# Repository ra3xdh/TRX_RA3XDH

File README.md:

## Описание

Схема и печатная плата для улучшенной версии моего трансивера из журнала Радио №2, 2009.

Видео его работы здесь: https://www.youtube.com/watch?v=EY1k9Iahgxw

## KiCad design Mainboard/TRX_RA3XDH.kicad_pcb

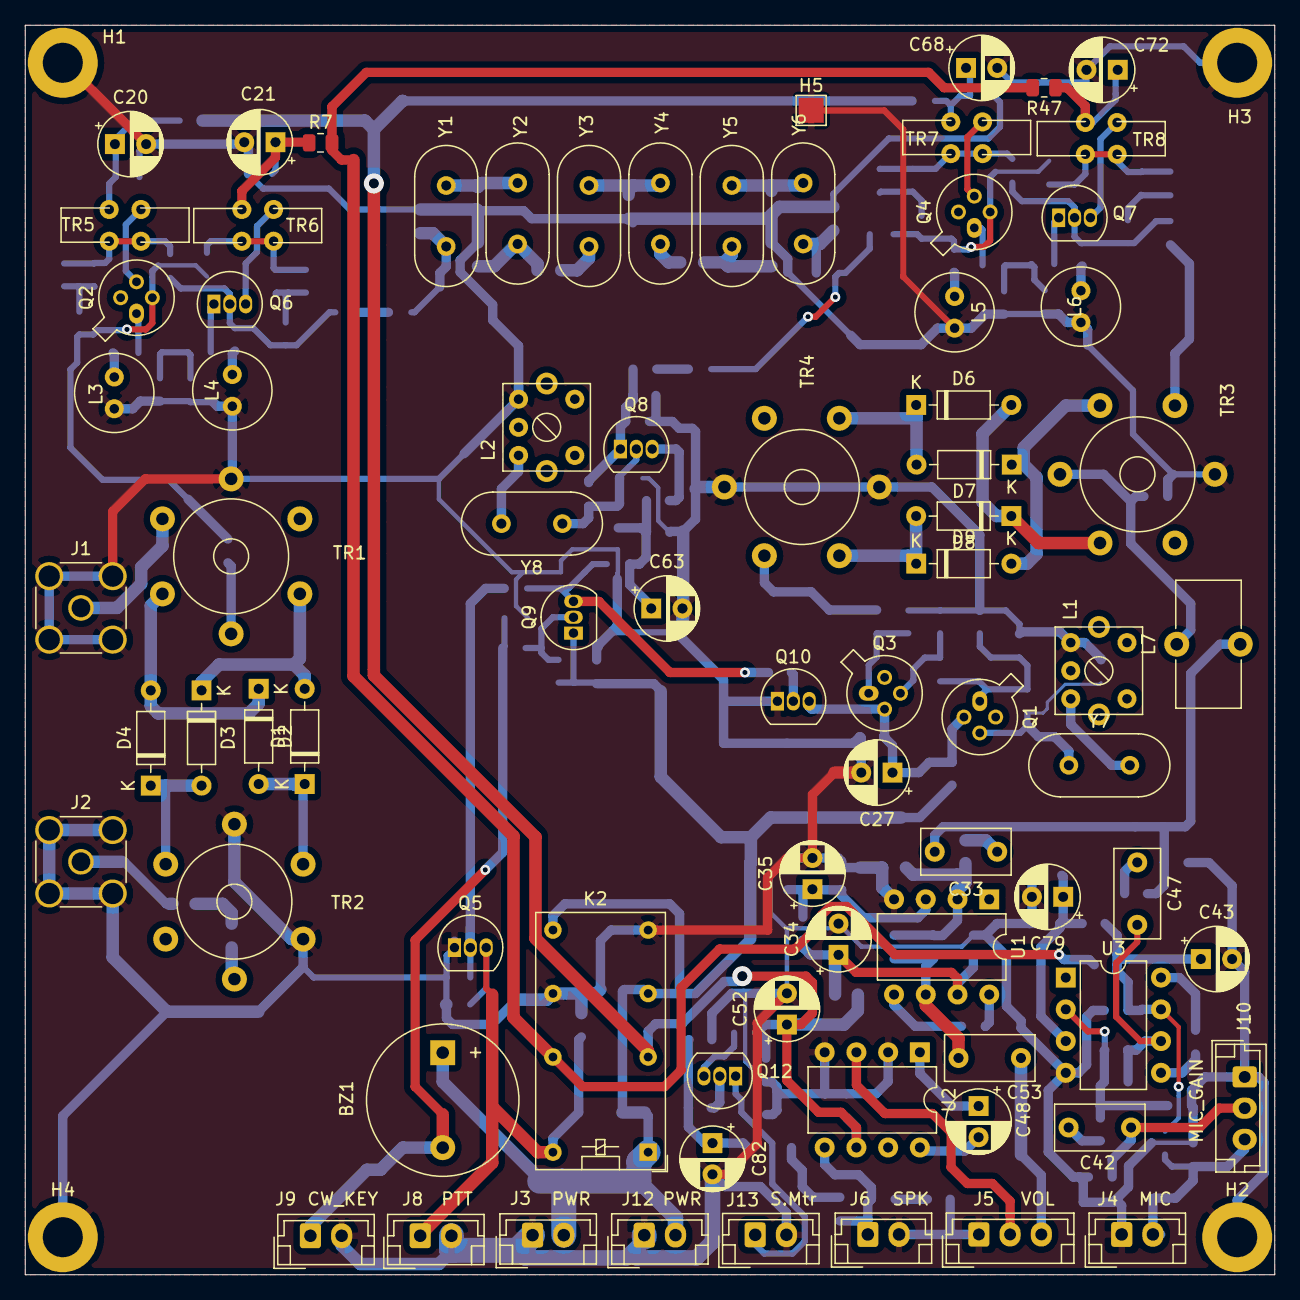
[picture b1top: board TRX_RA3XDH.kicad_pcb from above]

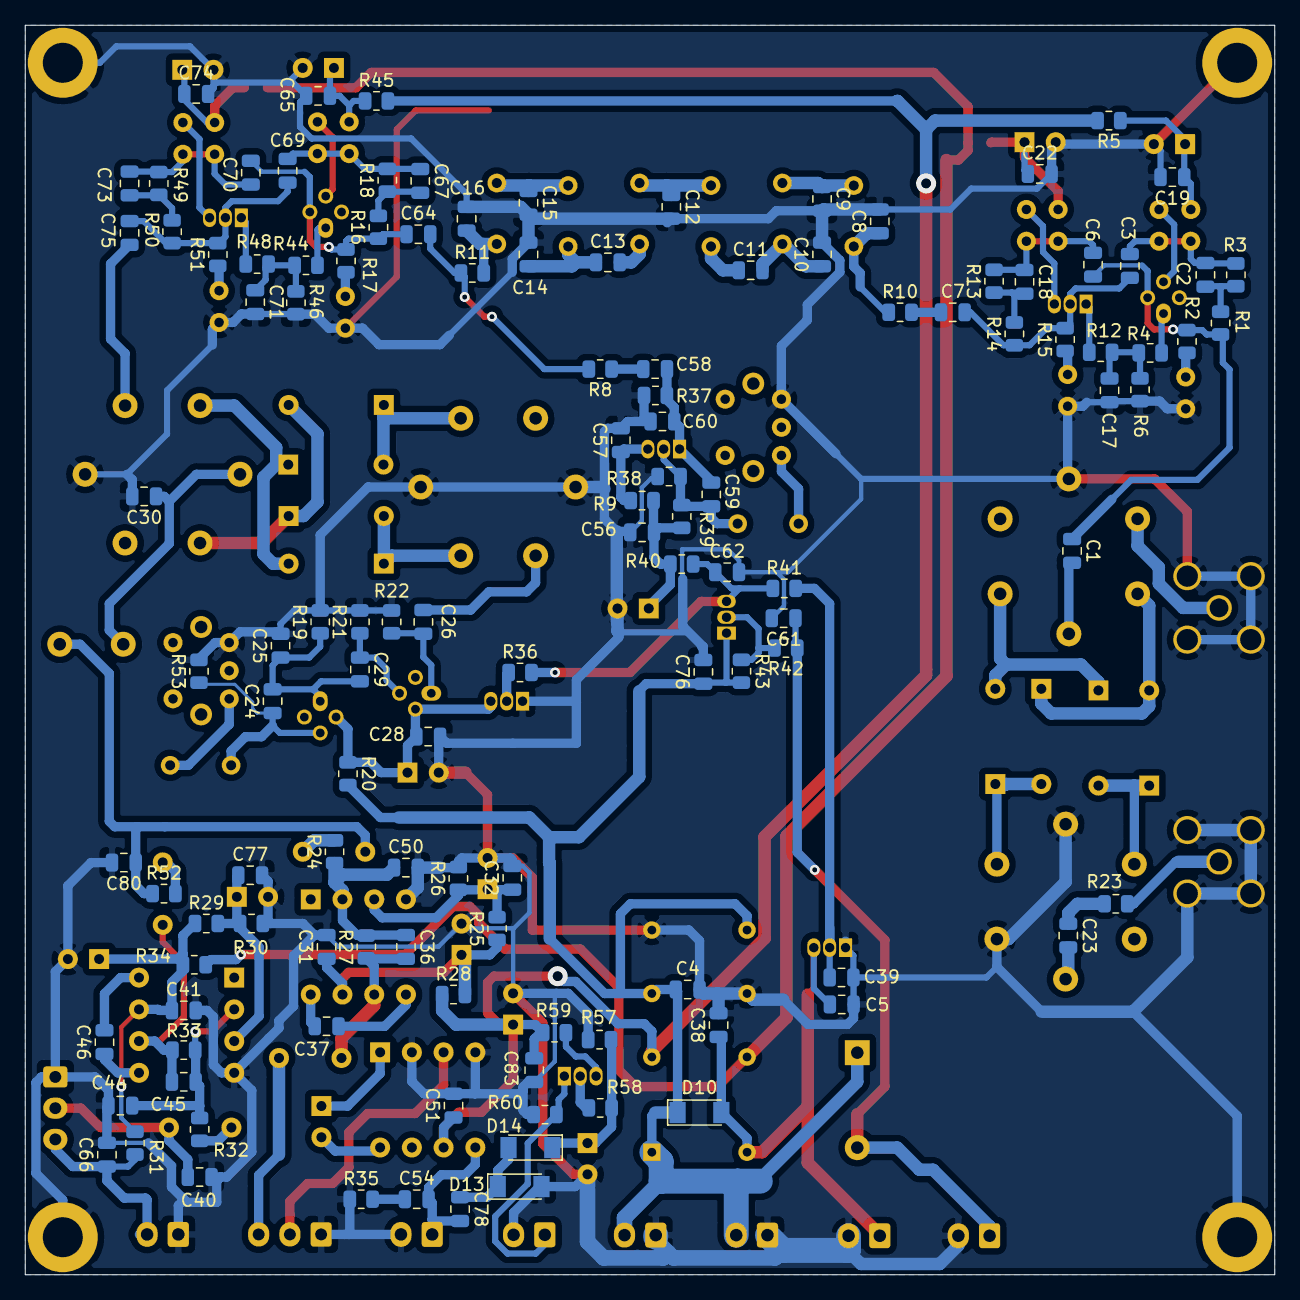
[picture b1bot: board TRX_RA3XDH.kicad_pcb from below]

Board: 2 copper layers, 100.0 x 100.0 mm, 203 parts (121 on the bottom side), 108 nets.

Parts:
BZ1: Buzzer; Buzzer_12x9.5RM7.6
C1, C3, C6, C7, C23, C26, C64, C69, C70: 10n; C_0805_2012Metric
C2, C4, C5, C17, C18, C19, C22, C28, C31, C32, C38, C39, C41, C51, C54, C56, C57, C61, C62, C65, C67, C71, C73, C74, C75, C76, C77, C78, C83: 0.1u; C_0805_2012Metric
C8, C16: 43p; C_0805_2012Metric
C9, C15: 94p; C_0805_2012Metric
C10, C14: 120p; C_0805_2012Metric
C11, C13: 370p; C_0805_2012Metric
C12: 130p; C_0805_2012Metric
C20, C21, C27, C34, C35, C43, C48, C52, C63, C68, C72, C79: 10u; CP_Radial_D5.0mm_P2.50mm
C24, C25, C58, C59, C60: 22p; C_0805_2012Metric
C29, C37, C46: 33p; C_0805_2012Metric
C30, C40, C44, C50, C66, C80: 47n; C_0805_2012Metric
C33, C42, C47, C53: 1.0; C_Rect_L7.0mm_W3.5mm_P5.00mm
C36: 680p; C_0805_2012Metric
C45: 1000p; C_0805_2012Metric
C82: 4.7u; CP_Radial_D5.0mm_P2.50mm
D1, D2, D3, D4, D6, D7, D8, D9: 1N5711; D_DO-35_SOD27_P7.62mm_Horizontal
D10, D13, D14: LL4148; D_MiniMELF
H1, H2, H3, H4: GND; MountingHole_3.2mm_M3_DIN965_Pad
H5: gnd; TestPoint_Pad_2.0x2.0mm
J1: RF_INOUT; SMA_Amphenol_132291_Vertical
J2: VFO; SMA_Amphenol_132291_Vertical
J3, J12: PWR; JST_EH_B2B-EH-A_1x02_P2.50mm_Vertical
J4: MIC; JST_EH_B2B-EH-A_1x02_P2.50mm_Vertical
J5: VOL; JST_EH_B3B-EH-A_1x03_P2.50mm_Vertical
J6: SPK; JST_EH_B2B-EH-A_1x02_P2.50mm_Vertical
J8: PTT; JST_EH_B2B-EH-A_1x02_P2.50mm_Vertical
J9: CW_KEY; JST_EH_B2B-EH-A_1x02_P2.50mm_Vertical
J10: MIC_GAIN; JST_EH_B3B-EH-A_1x03_P2.50mm_Vertical
J13: S-Met.; JST_EH_B2B-EH-A_1x02_P2.50mm_Vertical
K2: G5V-2; Relay_DPDT_Omron_G5V-2
L1, L2: 3u; NEOSID_5t_4.5x4.5mm_132
L3, L4, L5, L6: 33u; L2.5x6
L7: 33u; L_Toroid_Vertical_L10.0mm_W5.0mm_P5.08mm
Q1, Q3: 2N4416; TO-72-4
Q2, Q4: 2N918; TO-72-4
Q5, Q6, Q7, Q8, Q10, Q12: 2N3904; TO-92_Inline
Q9: 2N3906; TO-92_Inline
R1, R2, R14, R15, R16, R17, R22, R50, R51: 470; R_0805_2012Metric
R3, R13, R18, R49: 2.2k; R_0805_2012Metric
R4, R12, R35, R44, R48: 4.7; R_0805_2012Metric
R5, R7, R8, R10, R11, R45, R47: 47; R_0805_2012Metric
R6, R9, R28, R34, R40, R46: 100; R_0805_2012Metric
R19, R20: 680; R_0805_2012Metric
R21, R53: 10k; R_0805_2012Metric
R23: 33; R_0805_2012Metric
R24, R32, R52, R60: 1k; R_0805_2012Metric
R25, R26, R29, R30, R31: 20k; R_0805_2012Metric
R27: 120k; R_0805_2012Metric
R33: 33k; R_0805_2012Metric
R36, R41, R42, R43: 22k; R_0805_2012Metric
R37: 360; R_0805_2012Metric
R38: 6.8k; R_0805_2012Metric
R39: 13k; R_0805_2012Metric
R57: 1M; R_0805_2012Metric
R58: 150k; R_0805_2012Metric
R59: 8.2k; R_0805_2012Metric
TR1, TR2, TR3, TR4: FT37-43; Transformer_Toroid_Tapped_Horizontal_D9.0mm_Amidon-T30
TR5, TR6, TR7, TR8: FT37-43; L_Toroid_Vertical_L10.0mm_W5.0mm_4pin
U1, U3: NE5534; DIP-8_W7.62mm
U2: LM386; DIP-8_W7.62mm
Y1, Y2, Y3, Y4, Y5, Y6, Y7, Y8: 8.867Mhz; Crystal_HC49-U_Vertical

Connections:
+12V: BZ1.1, C4.1, C76.1, D10.1, J3.2, J12.2, K2.1, K2.6, K2.9, Q9.1, R20.2, R43.2
/+12V_BFO2: C62.1, Q9.3, R36.2, R40.2, R41.1
/+12V_RX: C51.1, C52.1, C83.1, K2.4, R5.2, R28.1, R45.2, R59.2, U2.6
/+12V_TX: K2.13, R7.2, R34.1, R47.2
/CW_KEY: BZ1.2, C61.1, J9.1, R42.1
/MIC_IN: C40.1, C42.2, J10.2
/PTT: C5.1, C38.1, D10.2, J8.1, K2.16, Q5.3
/TX: C39.1, Q5.2, R41.2
/VGND_RX: C32.1, C35.1, R25.2, R26.1, U1.3
/VGND_TX: C77.1, C79.1, R29.2, R30.1, U3.3
/VOL_IN: C53.1, J5.3
/VOL_OUT: J5.2, U2.3
GND: C4.2, C5.2, C8.2, C9.2, C10.2, C12.2, C14.2, C15.2, C16.2, C17.2, C19.2, C20.2, C21.2, C22.2, C25.2, C27.2, C28.2, C30.2, C31.2, C32.2, C34.2, C35.2, C38.2, C39.2, C40.2, C41.2, C43.2, C44.2, C50.2, C51.2, C52.2, C56.2, C57.2, C60.2, C61.2, C62.2, C63.2, C65.2, C66.2, C68.2, C71.2, C72.2, C74.2, C76.2, C77.2, C79.2, C80.2, C82.2, C83.2, D13.2, H1.1, H2.1, H3.1, H4.1, H5.1, J1.2, J2.2, J3.1, J4.1, J5.1, J6.2, J8.2, J9.2, J10.1, J12.1, J13.2, K2.8, K2.11, L1.2, L2.2, L3.2, L4.2, L5.2, L6.2, Q5.1, Q10.1, R6.1, R19.2, R21.2, R22.2, R26.2, R30.2, R35.1, R37.2, R38.2, R46.1, R53.2, R57.2, R60.1, TR1.5, TR2.2, TR2.4, TR3.5, TR4.2, TR4.5, U1.4, U2.2, U2.4, U3.4
unnamed: C1.1, C6.2, Q2.2, R1.1, R2.2
unnamed: C1.2, TR1.2
unnamed: C2.1, C3.2, R3.2, TR5.1, TR5.3
unnamed: C2.2, R1.2, R3.1
unnamed: C3.1, C7.2, Q6.2, R14.1, R15.2
unnamed: C7.1, R10.2
unnamed: C8.1, R10.1, Y1.1
unnamed: C9.1, Y1.2, Y2.1
unnamed: C10.1, C11.2, Y2.2
unnamed: C11.1, Y3.1
unnamed: C12.1, Y3.2, Y4.1
unnamed: C13.1, C14.1, Y5.1
unnamed: C13.2, Y4.2
unnamed: C15.1, Y5.2, Y6.1
unnamed: C16.1, R11.2, Y6.2
unnamed: C17.1, R4.1, R6.2, R12.1
unnamed: C6.1, C18.1, R13.2, TR6.2, TR6.4
unnamed: C18.2, R13.1, R14.2
unnamed: C19.1, C20.1, R5.1, TR5.4
unnamed: C21.1, C22.1, R7.1, TR6.1
unnamed: C23.1, R23.1
unnamed: C23.2, TR2.5
unnamed: C24.1, Q1.3, R53.1, Y7.1
unnamed: C24.2, C25.1, C29.2, Q1.1, R19.1
unnamed: C26.1, Q3.1, R22.1
unnamed: C26.2, TR4.4
unnamed: C27.1, C28.1, Q1.2, Q3.2, Q10.3, R20.1
unnamed: C29.1, Q3.3, R21.1
unnamed: C30.1, L7.1, TR3.2
unnamed: C31.1, C34.1, R25.1, R28.2, U1.7
unnamed: C33.1, R24.2
unnamed: C33.2, C80.1, L7.2, R52.1
unnamed: C36.1, C50.1, R24.1, R27.2, U1.2
unnamed: C36.2, C53.2, R27.1, U1.6
unnamed: C37.1, U1.5
unnamed: C37.2, U1.8
unnamed: C41.1, C43.1, R29.1, R31.1, R34.2, U3.7
unnamed: C42.1, R32.2
unnamed: C44.1, C45.1, R32.1, R33.2, U3.2
unnamed: C45.2, C47.2, R33.1, U3.6
unnamed: C46.1, U3.5
unnamed: C46.2, U3.8
unnamed: C47.1, R52.2
unnamed: C48.1, U2.1
unnamed: C48.2, U2.8
unnamed: C54.1, R35.2
unnamed: C54.2, C78.2, J6.1, U2.5
unnamed: C56.1, C63.1, R9.1, R39.1, R40.1
unnamed: C57.1, Q8.3, R9.2
unnamed: C58.1, C59.2, C60.1, Q8.1, R37.1
unnamed: C58.2, R8.1
unnamed: C59.1, Q8.2, R38.1, R39.2, Y8.1
unnamed: C64.1, C70.2, Q4.2, R16.1, R17.2
unnamed: C64.2, R8.2, R11.1
unnamed: C65.1, C68.1, R45.1, TR7.4
unnamed: C66.1, J4.2, J10.3, R31.2
unnamed: C67.1, C69.2, R18.2, TR7.1, TR7.3
unnamed: C67.2, R16.2, R18.1
unnamed: C69.1, C75.1, Q7.2, R50.1, R51.2
unnamed: C70.1, C73.1, R49.2, TR8.2, TR8.4
unnamed: C71.1, R44.1, R46.2, R48.1
unnamed: C72.1, C74.1, R47.1, TR8.1
unnamed: C73.2, R49.1, R50.2
unnamed: C75.2, TR3.4
unnamed: C78.1, D13.1, D14.2
unnamed: C82.1, D14.1, R57.1, R58.2
unnamed: D1.1, D2.2, TR2.1
unnamed: D1.2, D3.1, TR1.3
unnamed: D2.1, D4.2, TR1.1
unnamed: D3.2, D4.1, TR2.3
unnamed: D6.1, D7.2, TR4.3
unnamed: D6.2, D8.1, TR3.3
unnamed: D7.1, D9.2, TR3.1
unnamed: D8.2, D9.1, TR4.1
unnamed: J1.1, TR1.4
unnamed: J2.1, R23.2
unnamed: J13.1, Q12.1, R60.2
unnamed: L1.1, Y7.2
unnamed: L2.1, Y8.2
unnamed: L3.1, R2.1
unnamed: L4.1, R15.1
unnamed: L5.1, R17.1
unnamed: L6.1, R51.1
unnamed: Q2.1, R4.2
unnamed: Q2.3, TR5.2
unnamed: Q4.1, R44.2
unnamed: Q4.3, TR7.2
unnamed: Q6.1, R12.2
unnamed: Q6.3, TR6.3
unnamed: Q7.1, R48.2
unnamed: Q7.3, TR8.3
unnamed: Q9.2, R42.2, R43.1
unnamed: Q10.2, R36.1
unnamed: Q12.2, R58.1
unnamed: Q12.3, R59.1

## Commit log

2021-04-07 Added mainboard design files
2021-04-08 Added connectors labels
2021-04-11 Added README
2021-04-11 Add schermatic
